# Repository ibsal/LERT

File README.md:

LERT - Liquid Engine Rocket Team

LERT will launch humans to space in 2 months, please give me 10 trillion dollars pls

AD ASTRA PER IRAM

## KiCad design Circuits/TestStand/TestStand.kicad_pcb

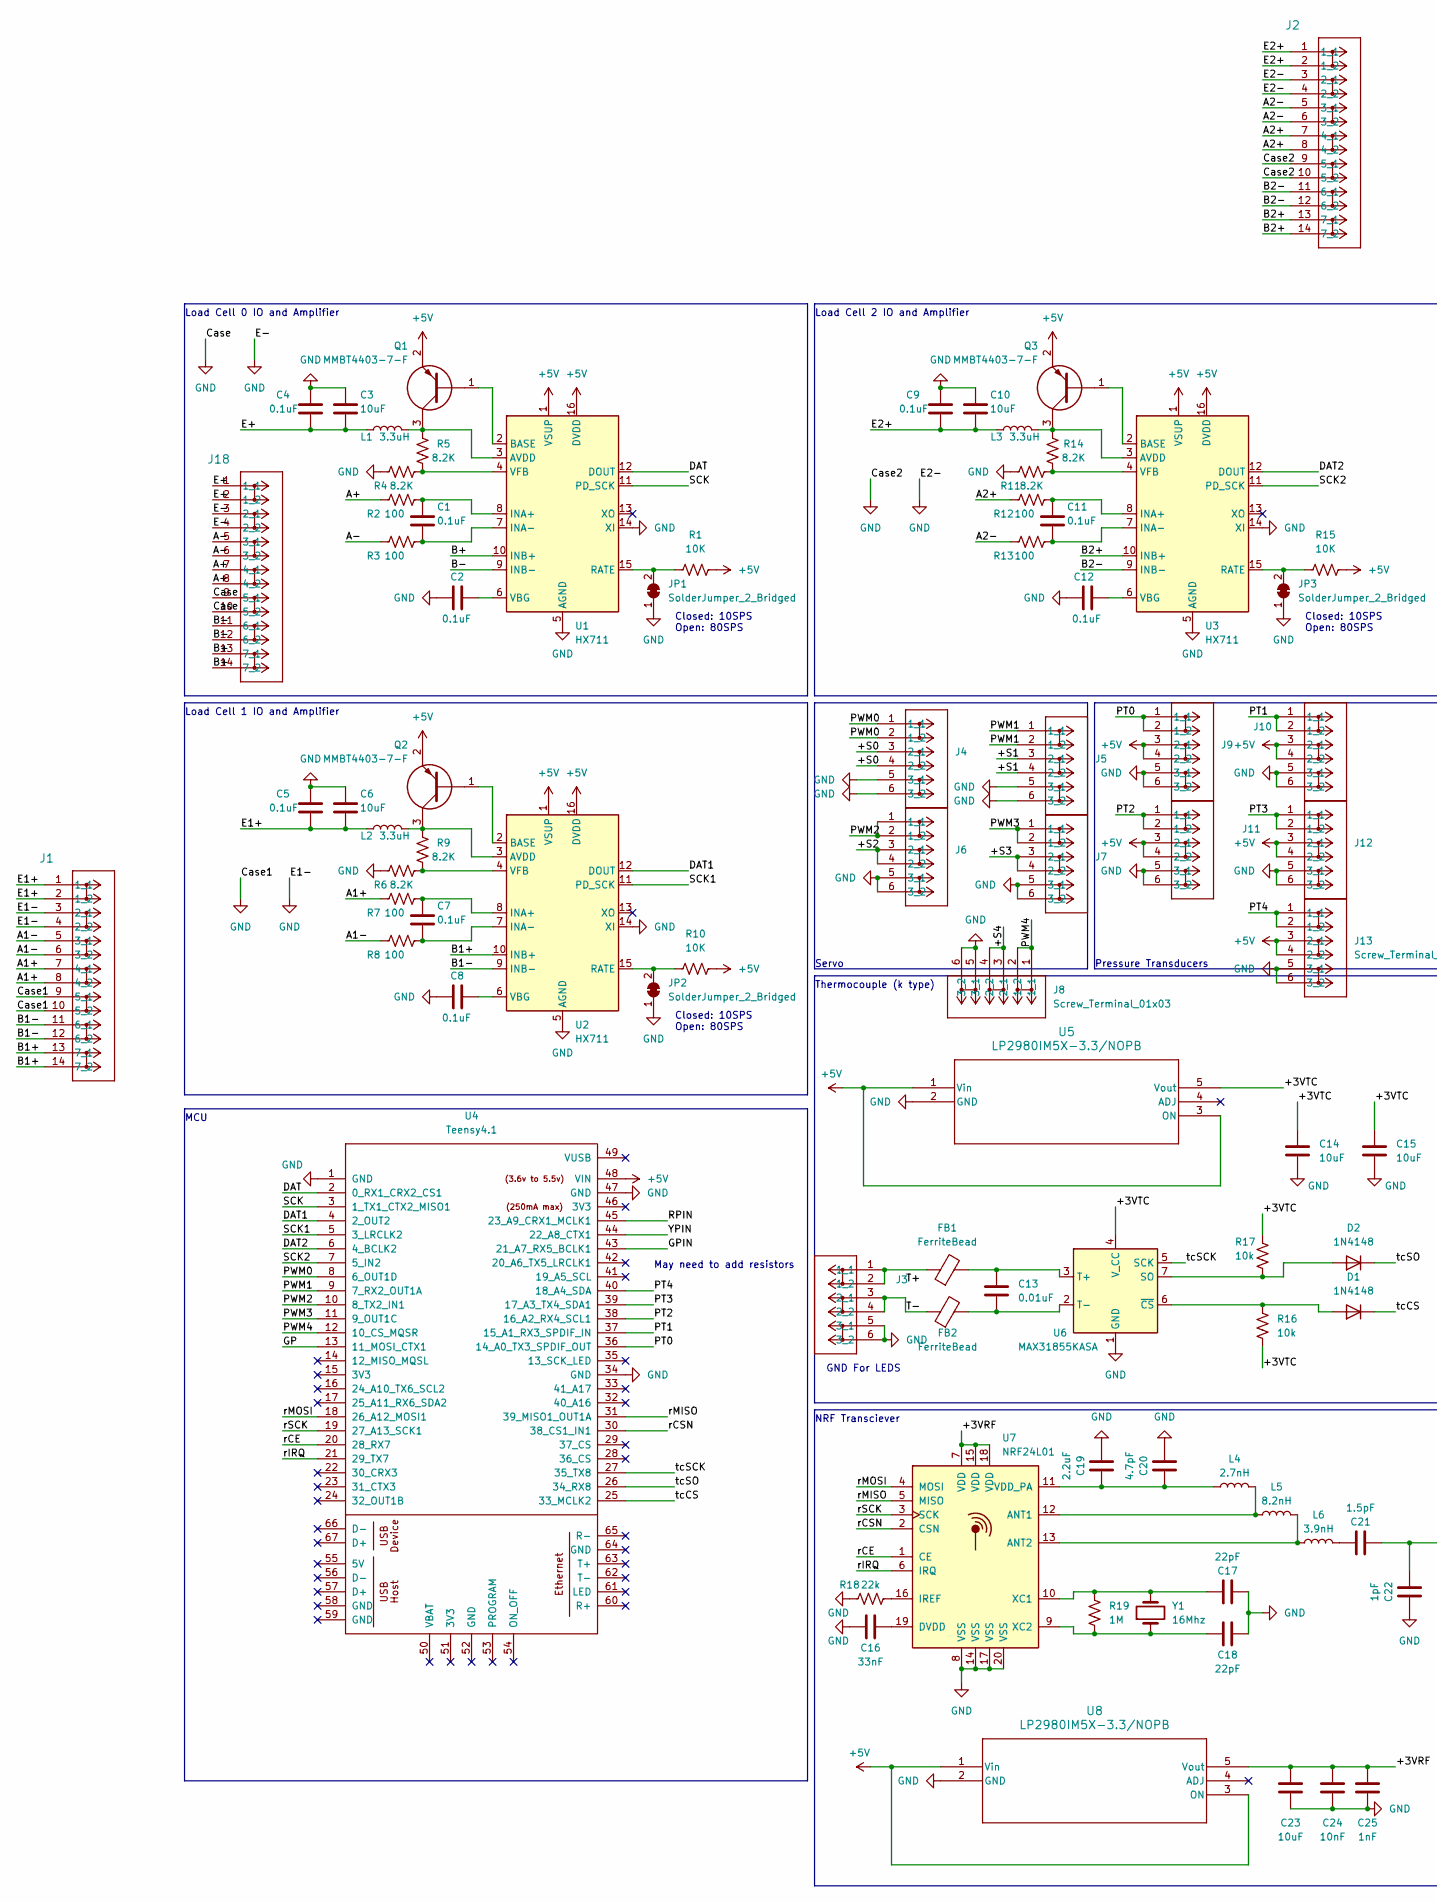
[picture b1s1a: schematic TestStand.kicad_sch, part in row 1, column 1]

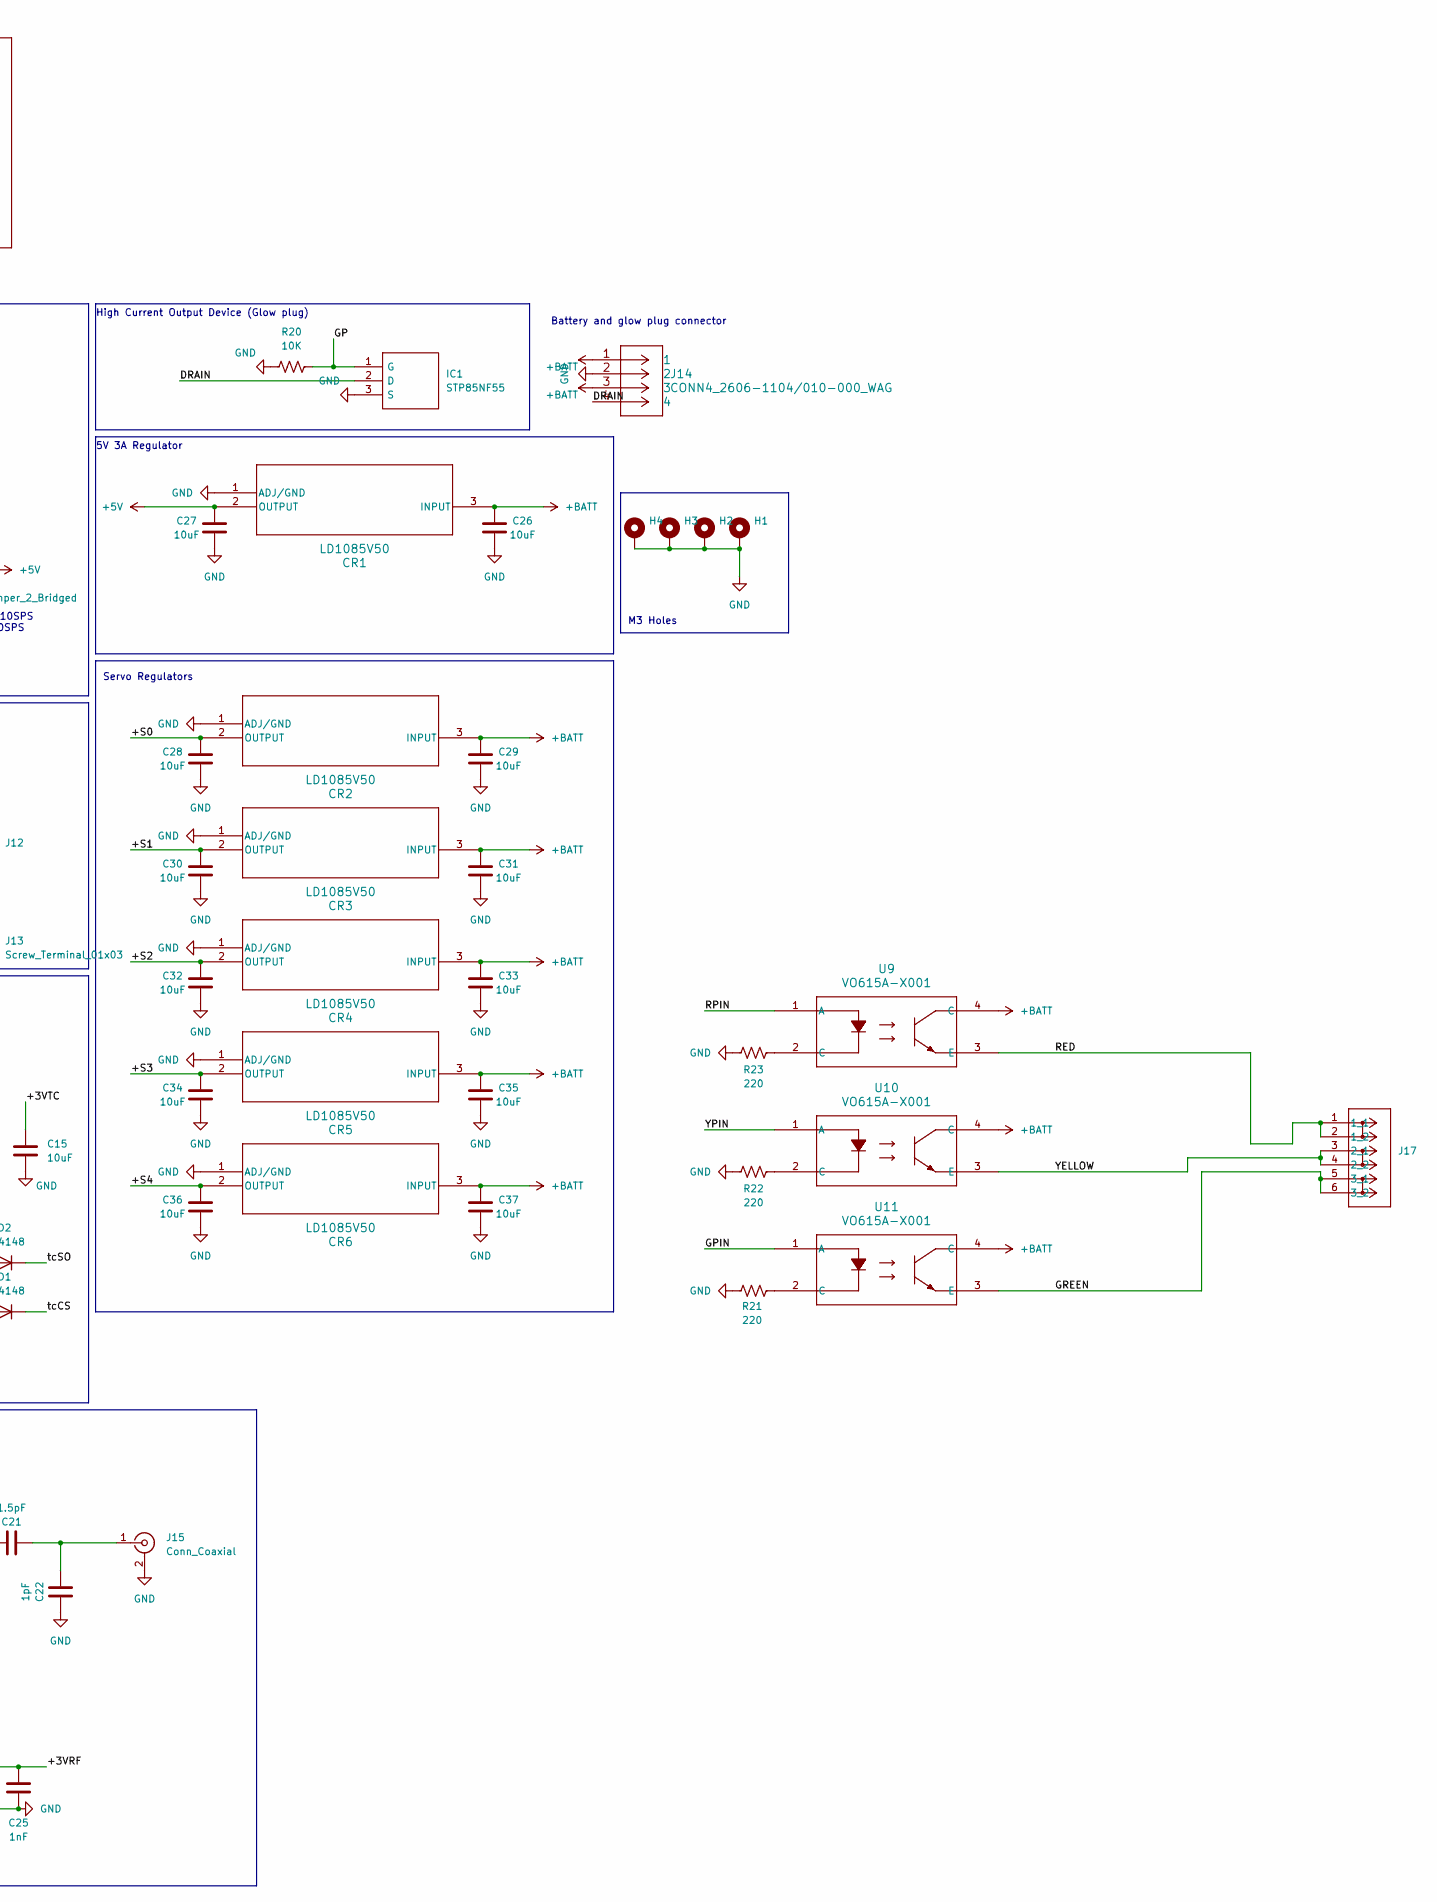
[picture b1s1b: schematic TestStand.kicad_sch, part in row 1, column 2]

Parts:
C1, C2, C4, C5, C7, C8, C9, C11, C12: 0.1uF; C_0805_2012Metric; LCSC C126469
C3, C6, C10, C14, C15, C23, C26, C27, C28, C29, C30, C31, C32, C33, C34, C35, C36, C37: 10uF; C_0805_2012Metric; LCSC C15850
C13: 0.01uF; C_0805_2012Metric; LCSC C1710
C16: 33nF; C_0805_2012Metric; LCSC C1739
C17, C18: 22pF; C_0805_2012Metric; LCSC C1804
C19: 2.2uF; C_0805_2012Metric; LCSC C377773
C20: 4.7pF; C_0805_2012Metric; LCSC C519993
C21: 1.5pF; C_0805_2012Metric; LCSC C1788
C22: 1pF; C_0805_2012Metric; LCSC C1786
C24: 10nF; C_0805_2012Metric; LCSC C1710
C25: 1nF; C_0805_2012Metric; LCSC C46653
CR1, CR2, CR3, CR4, CR5, CR6: LD1085V50; TO-220_STM; LCSC C283283
D1, D2: 1N4148; D_DO-35_SOD27_P7.62mm_Horizontal
FB1, FB2: FerriteBead; L_0805_2012Metric
H1, H2, H3, H4: MountingHole_Pad; MountingHole_3.2mm_M3_Pad
IC1: STP85NF55; TO255P460X1020X2008-3P; Mouser Part Number 511-STP85NF55
J1, J2, J18: 2601-1107; CONN7_2601-1107_WAG
J3, J4, J5, J6, J7, J8, J9, J10, J11, J12, J13, J17: Screw_Terminal_01x03; CONN3_2601-1103_WAG
J14: CONN4_2606-1104/010-000_WAG; 2606-1104&slash_010-000
J15: Conn_Coaxial; SMA_Molex_73251-1153_EdgeMount_Horizontal
JP1, JP2, JP3: SolderJumper_2_Bridged; SolderJumper-2_P1.3mm_Bridged_RoundedPad1.0x1.5mm
L1, L2, L3: 3.3uH; L_0402_1005Metric; LCSC C84474
L4: 2.7nH; L_0402_1005Metric; LCSC C77108
L5: 8.2nH; L_0402_1005Metric; LCSC C76778
L6: 3.9nH; L_0402_1005Metric; LCSC C14033
Q1, Q2, Q3: MMBT4403-7-F; SOT96P240X110-3N; Mouser Part Number 621-MMBT4403-F
R1, R10, R15, R20: 10K; R_0805_2012Metric; LCSC C17414
R2, R3, R7, R8, R12, R13: 100; R_0805_2012Metric; LCSC C17408
R4, R5, R6, R9, R11, R14: 8.2K; R_0805_2012Metric; LCSC C17828
R16, R17: 10k; R_0805_2012Metric; LCSC C17414
R18: 22k; R_0805_2012Metric; LCSC C17560
R19: 1M; R_0805_2012Metric; LCSC C17514
R21, R22, R23: 220; R_0805_2012Metric
U1, U2, U3: HX711; SOP-16_3.9x9.9mm_P1.27mm; LCSC C6705483
U4: Teensy4.1; Teensy41
U5, U8: LP2980IM5X-3.3/NOPB; MF05A_TEX; LCSC C88715
U6: MAX31855KASA; SOIC-8_3.9x4.9mm_P1.27mm; LCSC C52028
U7: NRF24L01; QFN-20-1EP_4x4mm_P0.5mm_EP2.5x2.5mm; LCSC C8791
U9, U10, U11: VO615A-X001; DIP-4_VO615A_VIS
Y1: 16Mhz; Crystal_SMD_5032-2Pin_5.0x3.2mm; LCSC C122519

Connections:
+5V: C27.2, CR1.2 (OUTPUT), J9.3 (2_1), J9.4 (2_2), J10.3 (2_1), J10.4 (2_2), J11.3 (2_1), J11.4 (2_2), J12.3 (2_1), J12.4 (2_2), J13.3 (2_1), J13.4 (2_2), Q1.2, Q2.2, Q3.2, R1.2, R10.2, R15.2, U1.1 (VSUP), U1.16 (DVDD), U2.1 (VSUP), U2.16 (DVDD), U3.1 (VSUP), U3.16 (DVDD), U4.48 (VIN), U5.1 (Vin), U5.3 (ON), U8.1 (Vin), U8.3 (ON)
+BATT: C26.2, C29.2, C31.2, C33.2, C35.2, C37.2, CR1.3 (INPUT), CR2.3 (INPUT), CR3.3 (INPUT), CR4.3 (INPUT), CR5.3 (INPUT), CR6.3 (INPUT), J14.1, J14.3, U9.4 (C), U10.4 (C), U11.4 (C)
/+3VRF: C23.2, C24.2, C25.2, U7.7 (VDD), U7.15 (VDD), U7.18 (VDD), U8.5 (Vout)
/+3VTC: C14.1, C15.1, R16.2, R17.1, U5.5 (Vout), U6.4 (V_CC)
/+S0: C28.2, CR2.2 (OUTPUT), J4.3 (2_1), J4.4 (2_2)
/+S1: C30.2, CR3.2 (OUTPUT), J5.3 (2_1), J5.4 (2_2)
/+S2: C32.2, CR4.2 (OUTPUT), J6.3 (2_1), J6.4 (2_2)
/+S3: C34.2, CR5.2 (OUTPUT), J7.3 (2_1), J7.4 (2_2)
/+S4: C36.2, CR6.2 (OUTPUT), J8.3 (2_1), J8.4 (2_2)
/A1+: J1.7 (4_1), J1.8 (4_2), R7.1
/A1-: J1.5 (3_1), J1.6 (3_2), R8.1
/A2+: J2.7 (4_1), J2.8 (4_2), R12.1
/A2-: J2.5 (3_1), J2.6 (3_2), R13.1
/A+: J18.7 (4_1), J18.8 (4_2), R2.1
/A-: J18.5 (3_1), J18.6 (3_2), R3.1
/B1+: J1.13 (7_1), J1.14 (7_2), U2.10 (INB+)
/B1-: J1.11 (6_1), J1.12 (6_2), U2.9 (INB-)
/B2+: J2.13 (7_1), J2.14 (7_2), U3.10 (INB+)
/B2-: J2.11 (6_1), J2.12 (6_2), U3.9 (INB-)
/B+: J18.13 (7_1), J18.14 (7_2), U1.10 (INB+)
/B-: J18.11 (6_1), J18.12 (6_2), U1.9 (INB-)
/DAT: U1.12 (DOUT), U4.2 (0_RX1_CRX2_CS1)
/DAT1: U2.12 (DOUT), U4.4 (2_OUT2)
/DAT2: U3.12 (DOUT), U4.6 (4_BCLK2)
/DRAIN: IC1.2 (D), J14.4
/E1+: C5.1, C6.1, J1.1 (1_1), J1.2 (1_2), L2.1
/E2+: C9.1, C10.1, J2.1 (1_1), J2.2 (1_2), L3.1
/E+: C3.1, C4.1, J18.1 (1_1), J18.2 (1_2), L1.1
/GP: IC1.1 (G), R20.2, U4.13 (11_MOSI_CTX1)
/GPIN: U4.43 (21_A7_RX5_BCLK1), U11.1 (A)
/GREEN: J17.5 (3_1), J17.6 (3_2), U11.3 (E)
/PT0: J9.1 (1_1), J9.2 (1_2), U4.36 (14_A0_TX3_SPDIF_OUT)
/PT1: J10.1 (1_1), J10.2 (1_2), U4.37 (15_A1_RX3_SPDIF_IN)
/PT2: J11.1 (1_1), J11.2 (1_2), U4.38 (16_A2_RX4_SCL1)
/PT3: J12.1 (1_1), J12.2 (1_2), U4.39 (17_A3_TX4_SDA1)
/PT4: J13.1 (1_1), J13.2 (1_2), U4.40 (18_A4_SDA)
/PWM0: J4.1 (1_1), J4.2 (1_2), U4.8 (6_OUT1D)
/PWM1: J5.1 (1_1), J5.2 (1_2), U4.9 (7_RX2_OUT1A)
/PWM2: J6.1 (1_1), J6.2 (1_2), U4.10 (8_TX2_IN1)
/PWM3: J7.1 (1_1), J7.2 (1_2), U4.11 (9_OUT1C)
/PWM4: J8.1 (1_1), J8.2 (1_2), U4.12 (10_CS_MQSR)
/RED: J17.1 (1_1), J17.2 (1_2), U9.3 (E)
/RPIN: U4.45 (23_A9_CRX1_MCLK1), U9.1 (A)
/SCK: U1.11 (PD_SCK), U4.3 (1_TX1_CTX2_MISO1)
/SCK1: U2.11 (PD_SCK), U4.5 (3_LRCLK2)
/SCK2: U3.11 (PD_SCK), U4.7 (5_IN2)
/T-: FB2.1, J3.3 (2_1), J3.4 (2_2)
/YELLOW: J17.3 (2_1), J17.4 (2_2), U10.3 (E)
/YPIN: U4.44 (22_A8_CTX1), U10.1 (A)
/rCE: U4.20 (28_RX7), U7.1 (CE)
/rCSN: U4.30 (38_CS1_IN1), U7.2 (CSN)
/rIRQ: U4.21 (29_TX7), U7.6 (IRQ)
/rMISO: U4.31 (39_MISO1_OUT1A), U7.5 (MISO)
/rMOSI: U4.18 (26_A12_MOSI1), U7.4 (MOSI)
/rSCK: U4.19 (27_A13_SCK1), U7.3 (SCK)
/tcCS: D1.1 (K), U4.25 (33_MCLK2)
/tcSCK: U4.27 (35_TX8), U6.5 (SCK)
/tcSO: D2.1 (K), U4.26 (34_RX8)
GND: C2.2, C3.2, C4.2, C5.2, C6.2, C8.2, C9.2, C10.2, C12.2, C14.2, C15.2, C16.1, C17.2, C18.2, C19.2, C20.2, C22.1, C23.1, C24.1, C25.1, C26.1, C27.1, C28.1, C29.1, C30.1, C31.1, C32.1, C33.1, C34.1, C35.1, C36.1, C37.1, CR1.1 (ADJ/GND), CR2.1 (ADJ/GND), CR3.1 (ADJ/GND), CR4.1 (ADJ/GND), CR5.1 (ADJ/GND), CR6.1 (ADJ/GND), H1.1, H2.1, H3.1, H4.1, IC1.3 (S), J1.3 (2_1), J1.4 (2_2), J1.9 (5_1), J1.10 (5_2), J2.3 (2_1), J2.4 (2_2), J2.9 (5_1), J2.10 (5_2), J3.5 (3_1), J3.6 (3_2), J4.5 (3_1), J4.6 (3_2), J5.5 (3_1), J5.6 (3_2), J6.5 (3_1), J6.6 (3_2), J7.5 (3_1), J7.6 (3_2), J8.5 (3_1), J8.6 (3_2), J9.5 (3_1), J9.6 (3_2), J10.5 (3_1), J10.6 (3_2), J11.5 (3_1), J11.6 (3_2), J12.5 (3_1), J12.6 (3_2), J13.5 (3_1), J13.6 (3_2), J14.2, J15.2 (Ext), J18.3 (2_1), J18.4 (2_2), J18.9 (5_1), J18.10 (5_2), JP1.1 (A), JP2.1 (A), JP3.1 (A), R4.1, R6.1, R11.1, R18.1, R20.1, R21.1, R22.1, R23.1, U1.5 (AGND), U1.14 (XI), U2.5 (AGND), U2.14 (XI), U3.5 (AGND), U3.14 (XI), U4.1 (GND), U4.34 (GND), U4.47 (GND), U5.2 (GND), U6.1 (GND), U7.8 (VSS), U7.14 (VSS), U7.17 (VSS), U7.20 (VSS), U8.2 (GND)
unnamed: C21.1, L6.2
unnamed: D1.2 (A), R16.1, U6.6 (~CS)
unnamed: D2.2 (A), R17.2, U6.7 (SO)
unnamed: FB1.1, J3.1 (1_1), J3.2 (1_2)
unnamed: C21.2, C22.2, J15.1 (In)
unnamed: JP1.2 (B), R1.1, U1.15 (RATE)
unnamed: JP2.2 (B), R10.1, U2.15 (RATE)
unnamed: JP3.2 (B), R15.1, U3.15 (RATE)
unnamed: R21.2, U11.2 (C)
unnamed: R22.2, U10.2 (C)
unnamed: R23.2, U9.2 (C)
unnamed: L1.2, Q1.3, R5.1, U1.3 (AVDD)
unnamed: Q1.1, U1.2 (BASE)
unnamed: C1.2, R2.2, U1.8 (INA+)
unnamed: C1.1, R3.2, U1.7 (INA-)
unnamed: C2.1, U1.6 (VBG)
unnamed: R4.2, R5.2, U1.4 (VFB)
unnamed: L2.2, Q2.3, R9.1, U2.3 (AVDD)
unnamed: Q2.1, U2.2 (BASE)
unnamed: C7.2, R7.2, U2.8 (INA+)
unnamed: C7.1, R8.2, U2.7 (INA-)
unnamed: C8.1, U2.6 (VBG)
unnamed: R6.2, R9.2, U2.4 (VFB)
unnamed: L3.2, Q3.3, R14.1, U3.3 (AVDD)
unnamed: Q3.1, U3.2 (BASE)
unnamed: C11.2, R12.2, U3.8 (INA+)
unnamed: C11.1, R13.2, U3.7 (INA-)
unnamed: C12.1, U3.6 (VBG)
unnamed: R11.2, R14.2, U3.4 (VFB)
unnamed: C13.1, FB1.2, U6.3 (T+)
unnamed: C13.2, FB2.2, U6.2 (T-)
unnamed: L4.2, L5.1, U7.12 (ANT1)
unnamed: L5.2, L6.1, U7.13 (ANT2)
unnamed: C16.2, U7.19 (DVDD)
unnamed: R18.2, U7.16 (IREF)
unnamed: C19.1, C20.1, L4.1, U7.11 (VDD_PA)
unnamed: C17.1, R19.1, U7.10 (XC1), Y1.2
unnamed: C18.1, R19.2, U7.9 (XC2), Y1.1

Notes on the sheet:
Closed: 10SPS Open: 80SPS
Servo Regulators
Load Cell 0 IO and Amplifier
Battery and glow plug connector
High Current Output Device (Glow plug)
5V 3A Regulator
M3 Holes
Pressure Transducers
NRF Transciever
Load Cell 2 IO and Amplifier
GND For LEDS
MCU
May need to add resistors
Load Cell 1 IO and Amplifier
Thermocouple (k type)
Servo

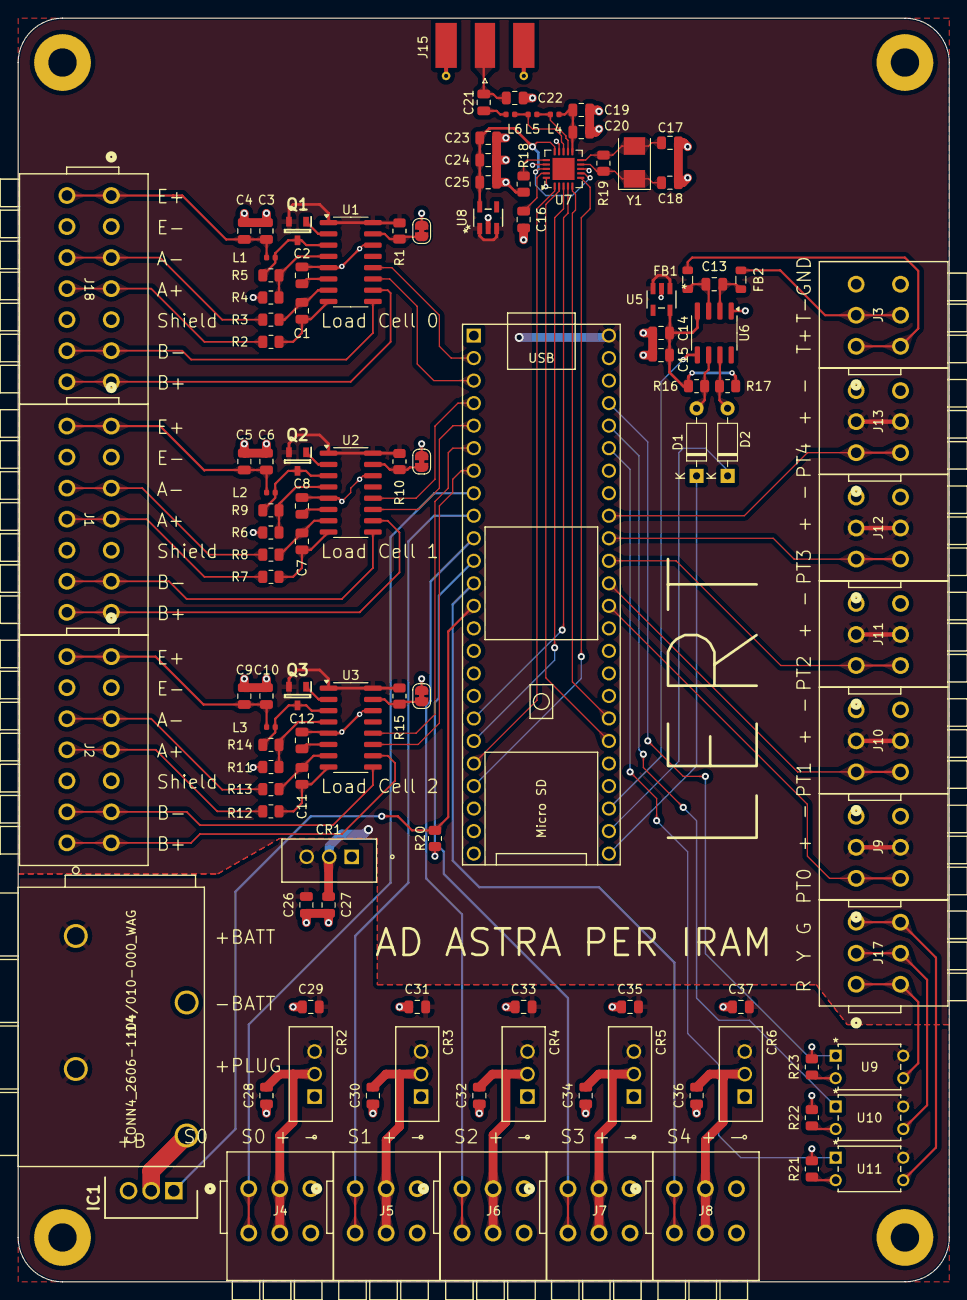
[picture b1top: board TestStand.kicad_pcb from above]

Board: 2 copper layers, 105.0 x 142.5 mm, 116 parts (0 on the bottom side), 97 nets.

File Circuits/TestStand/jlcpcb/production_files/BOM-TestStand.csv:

Comment,Designator,Footprint,LCSC
16Mhz,Y1,Crystal_SMD_5032-2Pin_5.0x3.2mm,C122519
0.1uF,"C1,C11,C12,C2,C4,C5,C7,C8,C9",C_0805_2012Metric,C126469
3.9nH,L6,L_0402_1005Metric,C14033
10uF,"C10,C14,C15,C23,C26,C27,C28,C29,C3,C30,C31,C32,C33,C34,C35,C36,C37,C6",C_0805_2012Metric,C15850
0.01uF,"C13,C24",C_0805_2012Metric,C1710
33nF,C16,C_0805_2012Metric,C1739
100,"R12,R13,R2,R3,R7,R8",R_0805_2012Metric,C17408
10K,"R1,R10,R15,R16,R17,R20",R_0805_2012Metric,C17414
1M,R19,R_0805_2012Metric,C17514
22k,R18,R_0805_2012Metric,C17560
8.2K,"R11,R14,R4,R5,R6,R9",R_0805_2012Metric,C17828
1pF,C22,C_0805_2012Metric,C1786
1.5pF,C21,C_0805_2012Metric,C1788
22pF,"C17,C18",C_0805_2012Metric,C1804
LD1085V50,"CR1,CR2,CR3,CR4,CR5,CR6",TO-220_STM,C283283
STP85NF55,IC1,TO255P460X1020X2008-3P,C3290239
2.2uF,C19,C_0805_2012Metric,C377773
1nF,C25,C_0805_2012Metric,C46653
4.7pF,C20,C_0805_2012Metric,C519993
MAX31855KASA,U6,SOIC-8_3.9x4.9mm_P1.27mm,C52028
HX711,"U1,U2,U3",SOP-16_3.9x9.9mm_P1.27mm,C6705483
8.2nH,L5,L_0402_1005Metric,C76778
2.7nH,L4,L_0402_1005Metric,C77108
3.3uH,"L1,L2,L3",L_0402_1005Metric,C84474
MMBT4403-7-F,"Q1,Q2,Q3",SOT96P240X110-3N,C85183
NRF24L01,U7,QFN-20-1EP_4x4mm_P0.5mm_EP2.5x2.5mm,C8791
LP2980IM5X-3.3/NOPB,"U5,U8",MF05A_TEX,C88715
1N4148,D1,D_DO-35_SOD27_P7.62mm_Horizontal,
SW_DIP_x01,SW1,SW_DIP_SPSTx01_Slide_6.7x4.1mm_W7.62mm_P2.54mm_LowProfile,
Conn_Coaxial,J15,SMA_Molex_73251-1153_EdgeMount_Horizontal,
FerriteBead,FB2,L_0805_2012Metric,
1N4148,D2,D_DO-35_SOD27_P7.62mm_Horizontal,
FerriteBead,FB1,L_0805_2012Metric,

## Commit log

2024-08-07 Hooray?
2024-08-07 yipee
2024-08-07 hooray
2024-08-08 HX711 Load Cell Circuitry
2024-08-08 Added all 3 load cell amplifiers
2024-08-08 Added rpi to schematic
2024-08-08 Deleted PI, added servos
2024-08-08 Added TEENSY libraries and teensy to schematic
2024-08-09 Added teensy footprint library
2024-08-09 Forgot if I commited or not
2024-08-13 Connected servo, pts, and load cells to mcu
2024-08-13 Started designing the PCB
2024-08-13 Added TC and RF circuits
2024-08-13 Connected TC and RF to mcu
2024-08-13 did some traces
2024-08-13 added glow plug circuitry to schematic
2024-08-13 added voltage regulator stuff
2024-08-14 Lots of tracing, filleting board shape
2024-08-14 started generating some gerbers
2024-08-14 Very important silkscreen additions
2024-08-14 Schematic cleanup
2024-08-14 assigned a bunch of components to real ones
2024-08-14 switched to the true connectors, did some rearranging, largely backwards progress :)
2024-08-14 fixed 3d models, arranged nicely
2024-08-14 Some more silkscreen final touches GO TO BED
2024-08-16 whatever I was working on last night
2024-08-16 added optoisolators and did some routing
2024-08-16 ALMOST DOWN ROUTING
2024-08-16 basically done
2024-08-16 exported board step
2024-09-18 Added analysis folder
2024-09-29 Started PV CAD
2024-09-29 adding stuffff
2024-09-29 idk what I changed
2025-03-03 help
2025-03-03 Param fixes and stuff
2025-04-15 Simulink model worked on
2025-04-29 Lots of engine modeling
2025-04-29 yeagh
2025-04-30 Cleanup of existing files, added cea transport interpolation fu nctions and documentation
2025-04-30 More organization
2025-04-30 one more
2025-05-05 Bartz is almost done
2025-05-06 Fixed Bartz
2025-05-07 YAHOO
2025-05-07 Modeled channel injector drop
2025-05-07 YAHHOOO
2025-05-19 Refactor
2025-05-20 Work on coupled model engine component
2025-05-22 Yippee now we have 3 interpolators
2025-05-25 So many changes
2025-05-25 FIXED NORMAL SHOCKS YAY
2025-05-26 Starting tank analysis in ernest
2025-09-01 created dashboard
2025-09-02 Data from hydrostatic testing

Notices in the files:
parts and their libraries:
Copyright 2016 Accelerated Designs. All rights reserved.
